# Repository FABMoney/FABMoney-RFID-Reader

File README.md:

A digital currency for FabLabs: Open Source Software, Hardware, Data, API, Design.
----------------------------------------------------------------------------------

FABMoney is an open source digital currency for enabling collaboration in a FabLab. The project is completely open source: software, data, hardware, design. 
More information coming soon also on [fabmoney.org](http://fabmoney.org).

Software is released under a [MIT License](http://opensource.org/licenses/mit-license.php/)

<br />This work is licensed under a <a rel="license" href="http://creativecommons.org/licenses/by/3.0/deed.en_US">Creative Commons Attribution 3.0 Unported License</a>.

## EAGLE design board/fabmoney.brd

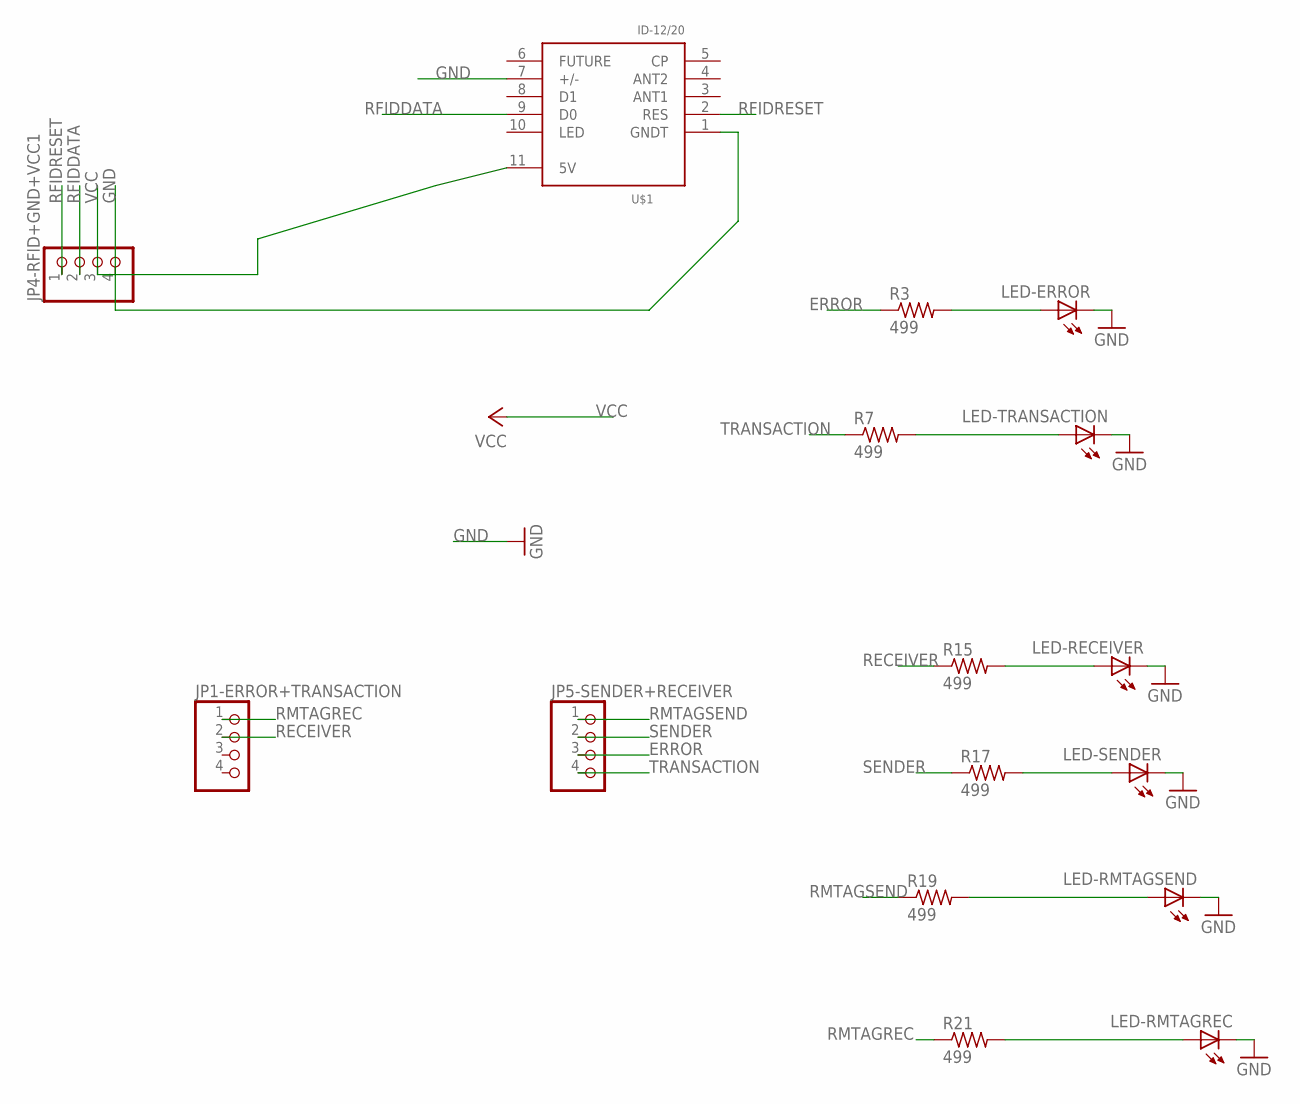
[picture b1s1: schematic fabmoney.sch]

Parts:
JP1-ERROR+TRANSACTION, JP4-RFID+GND+VCC1, JP5-SENDER+RECEIVER: PINHD-1X4; 1X04
LED-ERROR: LED5MM
LED-RECEIVER: LED5MM
LED-RMTAGREC: LED5MM
LED-RMTAGSEND: LED5MM
LED-SENDER: LED5MM
LED-TRANSACTION: LED5MM
R3, R7, R15, R17, R19, R21: 499; 1206
U$1: ID-12/20; ID-12

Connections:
ERROR: JP5-SENDER+RECEIVER.3, R3.1
GND: JP4-RFID+GND+VCC1.4, LED-ERROR.K (C), LED-RECEIVER.K (C), LED-RMTAGREC.K (C), LED-RMTAGSEND.K (C), LED-SENDER.K (C), LED-TRANSACTION.K (C), U$1.1 (GNDT), U$1.7 (+/-)
unnamed: LED-ERROR.A, R3.2
unnamed: LED-TRANSACTION.A, R7.2
unnamed: LED-RECEIVER.A, R15.2
unnamed: LED-SENDER.A, R17.2
unnamed: LED-RMTAGSEND.A, R19.2
unnamed: LED-RMTAGREC.A, R21.2
RECEIVER: JP1-ERROR+TRANSACTION.2, R15.1
RFIDDATA: JP4-RFID+GND+VCC1.2, U$1.9 (D0)
RFIDRESET: JP4-RFID+GND+VCC1.1, U$1.2 (RES)
RMTAGREC: JP1-ERROR+TRANSACTION.1, R21.1
RMTAGSEND: JP5-SENDER+RECEIVER.1, R19.1
SENDER: JP5-SENDER+RECEIVER.2, R17.1
TRANSACTION: JP5-SENDER+RECEIVER.4, R7.1
VCC: JP4-RFID+GND+VCC1.3, U$1.11 (5V)

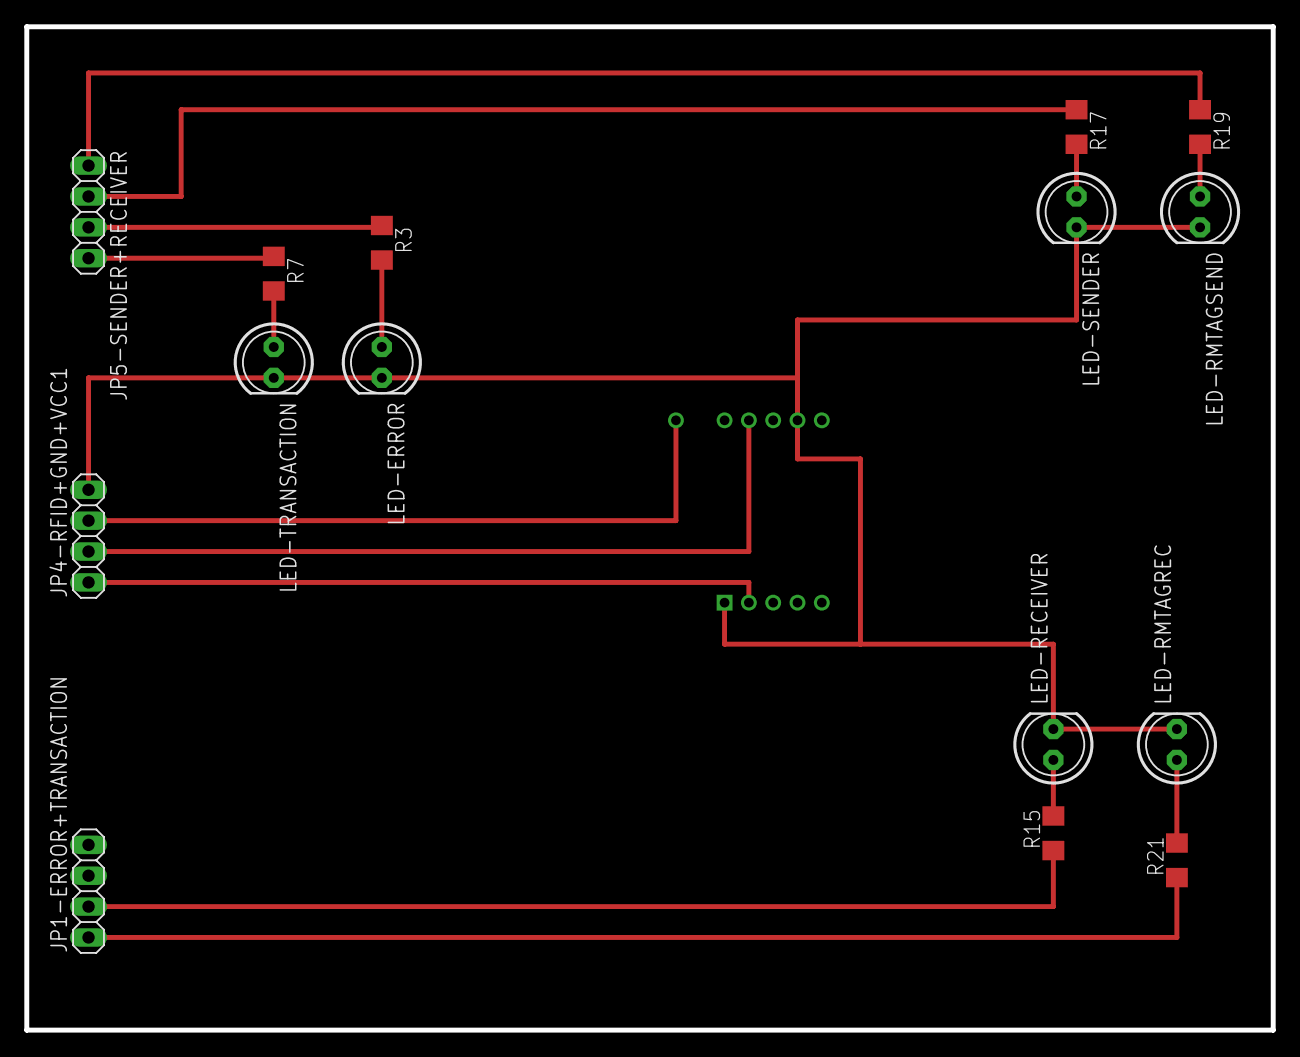
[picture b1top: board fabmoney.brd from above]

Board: 2 copper layers, 102.5 x 82.5 mm, 16 parts (1 on the bottom side), 16 nets.

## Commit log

2012-08-12 First commit: v.03 from FabAcademy
    This is the first commit: all the sources are the result of the work
    for the FabAcademy 2012, work done at Aalto FabLab (Aalto Media
    Factory, Helsinki) and FabLab Amsterdam (Waag, Amsterdam).
2012-08-12 Adding a doc folder for documentation
2012-08-12 Fixing a link to an image
2012-08-12 updating the main README.md file
2012-08-12 updating the README.md layout...
2012-08-12 Adding the licenses
2012-08-30 Adding some pictures to the doc folder
2012-08-30 Updating README.md a bit
